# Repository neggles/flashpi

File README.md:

# flashpi & nandpi

boards for turning a raspberry pi 

## Repository Structure

For the `flashpi` SPI flasher hat:

- `flashpi` contains the main schematics and board drawing
- `flashpi/flashpi.pretty` contains the board-specific footprints
- `flashpi/flashpi.3dshapes` contains the 3D models for parts on the board (and a bunch of extras from my various experiments)

For the `nandpi` Parallel NAND flasher hat (which is highly experimental):
- `nandpi` contains the main schematics and board drawing
- `nandpi/nandpi.pretty` contains the board-specific footprints
- `nandpi/nandpi.3dshapes` contains the 3D models for parts on the board (and a bunch of extras from my various experiments)

## Building
Simply call `make` in the top-top level directory. The `build` directory will then contain:

- the main board
- zipped gerbers for the boards you can directly use for manufacturing
- zipped gerbers and SMT assembly BOM/position files for JLCPCB's SMT assembly service for the single-board version.

Makefile uses [Jan Mrázek](https://github.com/yaqwsx)'s [KiKit](https://github.com/yaqwsx/KiKit), which I cannot recommend enough, and therefore has to be available on your system.

Jan's [jlcparts](https://yaqwsx.github.io/jlcparts/) app was also extremely useful in narrowing down part choices based on what JLCPCB have available.

-----
### **IMPORTANT NOTE:** If you give JLCPCB these files as-is, *please* verify the orientation of every part before submitting.

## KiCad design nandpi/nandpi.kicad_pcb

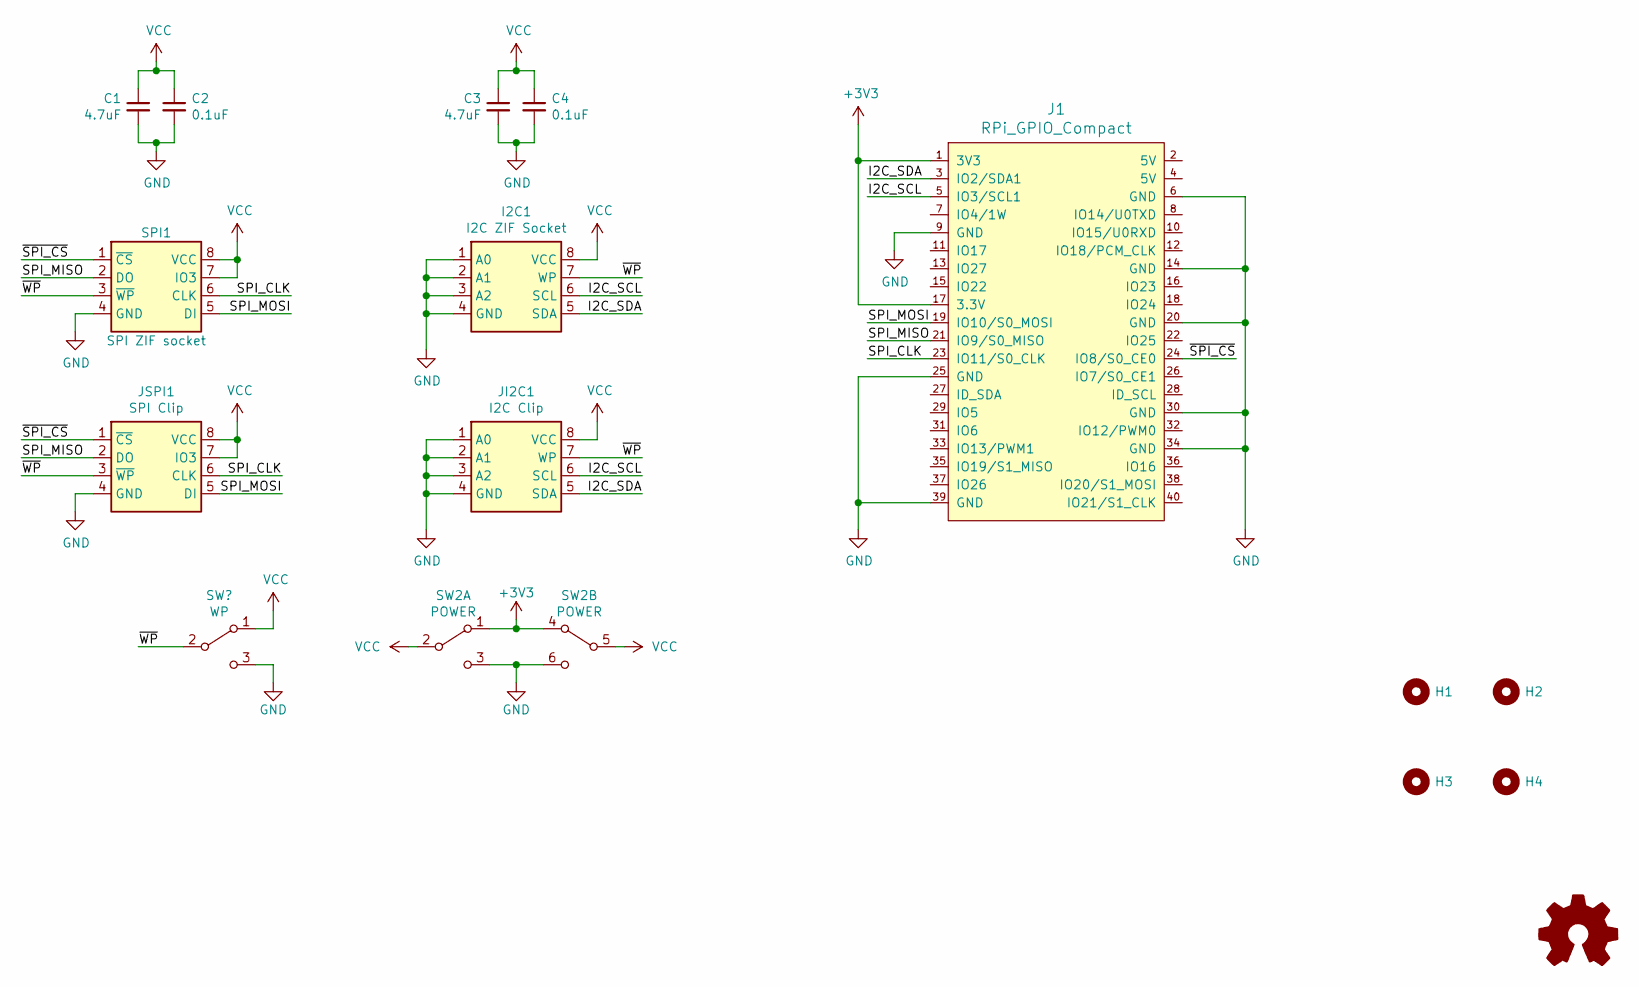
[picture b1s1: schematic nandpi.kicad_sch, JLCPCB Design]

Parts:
C1, C3: 4.7uF; C_0603_1608Metric_Pad1.05x0.95mm_HandSolder
C2, C4: 0.1uF; C_0402_1005Metric_Pad0.74x0.62mm_HandSolder
H1, H2, H3, H4: Pi; RPi_Hat_Mounting_Hole
I2C1: I2C ZIF Socket; Socket_ZIF_SOP_OTS-8(16)-1.27-03
J1: RPi_GPIO_Compact; Samtec_HLE-120-02-xxx-DV-BE-A_2x20_P2.54mm_Horizontal_3D
JI2C1: I2C Clip; IDC-Header_2x04_P2.54mm_Vertical
JSPI1: SPI Clip; IDC-Header_2x04_P2.54mm_Vertical
LOGO1: Logo_Open_Hardware_Small; neggle-logo-0.12
SPI1: SPI ZIF socket; Socket_ZIF_OTS-8(20)_1.27-01
SW2: POWER; SW-TH_SSSS213202

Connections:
+3V3: J1.1 (3V3), J1.17 (3.3V), SW2.1 (A), SW2.4 (A)
/I2C_SCL: I2C1.6 (SCL), J1.5 (IO3/SCL1), JI2C1.6 (SCL)
/I2C_SDA: I2C1.5 (SDA), J1.3 (IO2/SDA1), JI2C1.5 (SDA)
/SPI_CLK: J1.23 (IO11/S0_CLK), JSPI1.6 (CLK), SPI1.6 (CLK)
/SPI_MISO: J1.21 (IO9/S0_MISO), JSPI1.2 (DO), SPI1.2 (DO)
/SPI_MOSI: J1.19 (IO10/S0_MOSI), JSPI1.5 (DI), SPI1.5 (DI)
/~SPI_CS: J1.24 (IO8/S0_CE0), JSPI1.1 (~CS), SPI1.1 (~CS)
/~WP: I2C1.7 (WP), JI2C1.7 (WP), JSPI1.3 (~WP), SPI1.3 (~WP)
GND: C1.2, C2.2, C3.2, C4.2, I2C1.1 (A0), I2C1.2 (A1), I2C1.3 (A2), I2C1.4 (GND), J1.6 (GND), J1.9 (GND), J1.14 (GND), J1.20 (GND), J1.25 (GND), J1.30 (GND), J1.34 (GND), J1.39 (GND), JI2C1.1 (A0), JI2C1.2 (A1), JI2C1.3 (A2), JI2C1.4 (GND), JSPI1.4 (GND), SPI1.4 (GND), SW2.3 (C), SW2.6 (C); also elsewhere on the board
VCC: C1.1, C2.1, C3.1, C4.1, I2C1.8 (VCC), JI2C1.8 (VCC), JSPI1.7 (IO3), JSPI1.8 (VCC), SPI1.7 (IO3), SPI1.8 (VCC), SW2.2 (B), SW2.5 (B); also elsewhere on the board

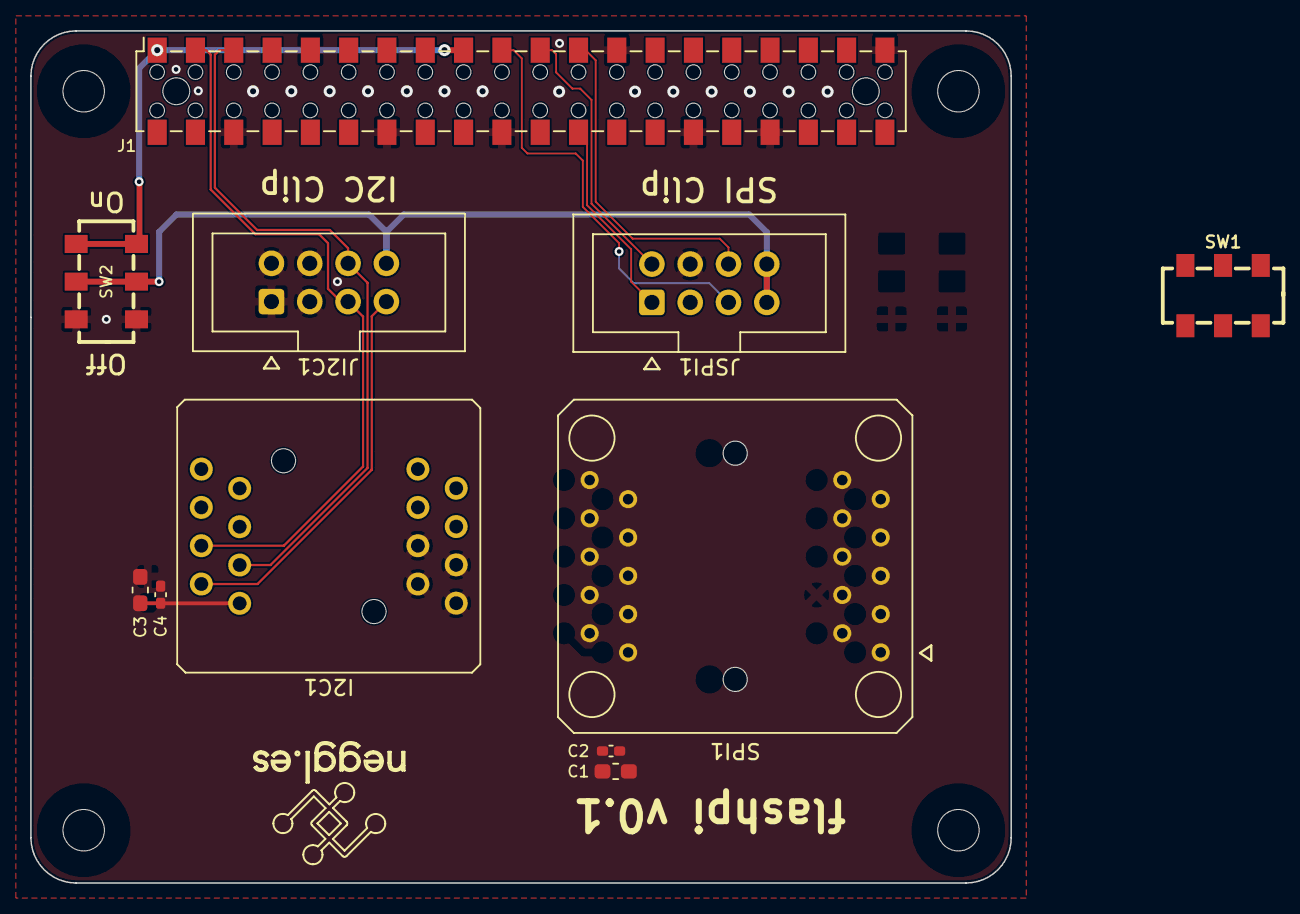
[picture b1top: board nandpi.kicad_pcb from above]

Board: 2 copper layers, 65.0 x 56.5 mm, 16 parts (0 on the bottom side), 10 nets.

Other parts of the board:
SW1: WRITE_PROTECT; SW-TH_SSSS213202

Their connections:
GND: SW1.3, SW1.6; also elsewhere on the board
VCC: SW1.1, SW1.4; also elsewhere on the board

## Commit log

2021-07-25 v0.1
2021-07-25 Initial gh-pages commit
2021-07-25 Deploying to gh-pages from @ neg2led/flashpi@78744ed3d378185e18bbcd1d40133a767380f805 🚀
2021-08-09 update makefile, minor tweaks
2021-08-09 fixup image link
2021-08-09 Deploying to gh-pages from @ neg2led/flashpi@cf96e1e5e2df5559336897a5176b93a9f1f65f92 🚀
2021-08-09 Deploying to gh-pages from @ neg2led/flashpi@0b6ba28f78260c705ec2badc80daa88c02d9d125 🚀
2021-12-06 update gitignore
2021-12-06 move flashpi to kicad nightly
2021-12-06 add nandpi as clone of flashpi
